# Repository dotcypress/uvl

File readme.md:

# UVL

UV Lamp PCB for 3mm LED's.

## License

Licensed under either of

- Apache License, Version 2.0 ([LICENSE-APACHE](LICENSE-APACHE) or
  http://www.apache.org/licenses/LICENSE-2.0)
- MIT license ([LICENSE-MIT](LICENSE-MIT) or http://opensource.org/licenses/MIT)

at your option.

### Contribution

Unless you explicitly state otherwise, any contribution intentionally submitted
for inclusion in the work by you, as defined in the Apache-2.0 license, shall be
dual licensed as above, without any additional terms or conditions.

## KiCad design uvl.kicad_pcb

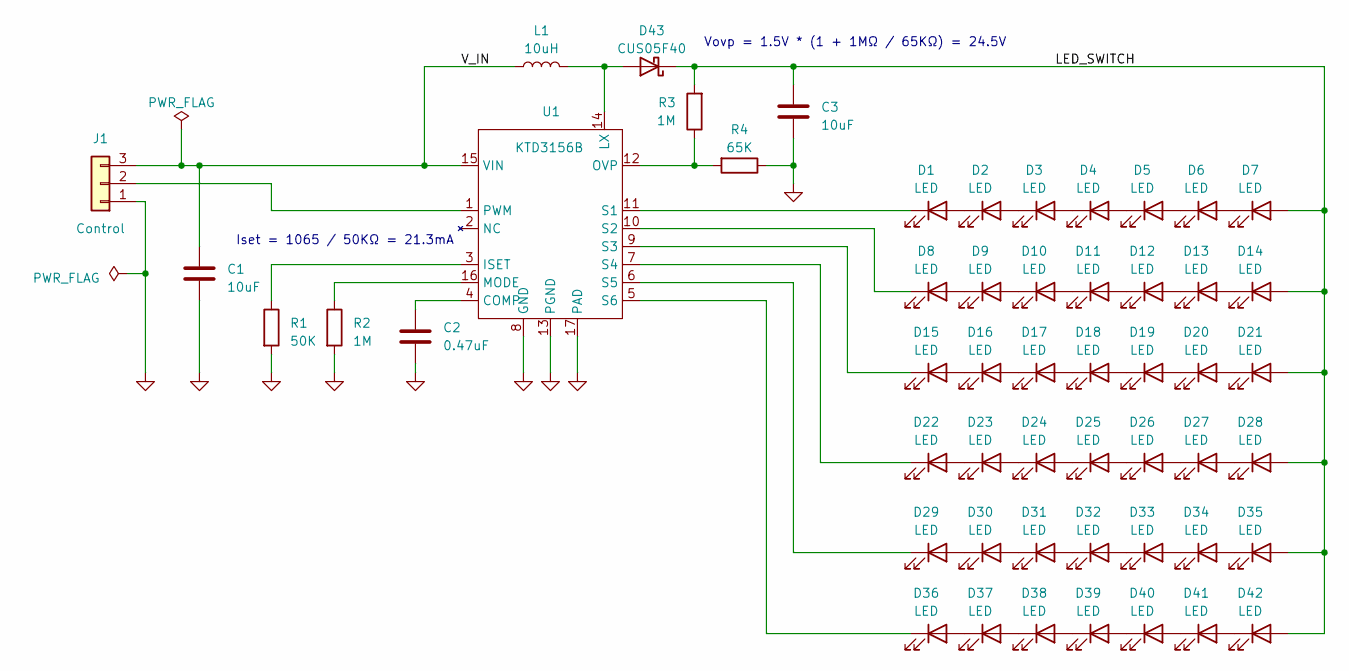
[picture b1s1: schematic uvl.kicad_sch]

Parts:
C1, C3: 10uF; C_0603_1608Metric
C2: 0.47uF; C_0603_1608Metric
D1, D2, D3, D4, D5, D6, D7, D8, D9, D10, D11, D12, D13, D14, D15, D16, D17, D18, D19, D20, D21, D22, D23, D24, D25, D26, D27, D28, D29, D30, D31, D32, D33, D34, D35, D36, D37, D38, D39, D40, D41, D42: LED; LED_D1.8mm_W3.3mm_H2.4mm
D43: CUS05F40; D_SOD-323_HandSoldering
J1: Control; PinHeader_1x03_P2.54mm_Vertical
L1: 10uH; L_Bourns-SRN6028
R1: 50K; R_0603_1608Metric
R2, R3: 1M; R_0603_1608Metric
R4: 65K; R_0603_1608Metric
U1: KTD3156B; QFN-16-1EP_3x3mm_P0.5mm_EP1.7x1.7mm

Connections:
/LED_SWITCH: C3.1, D7.2 (A), D14.2 (A), D21.2 (A), D28.2 (A), D35.2 (A), D42.2 (A), D43.1 (K), R3.2
/V_IN: C1.1, J1.3, L1.1, U1.15 (VIN)
GND: C1.2, C2.2, C3.2, J1.1, R1.2, R2.2, R4.1, U1.8 (GND), U1.13 (PGND), U1.17 (PAD)
unnamed: D1.2 (A), D2.1 (K)
unnamed: D1.1 (K), U1.11 (S1)
unnamed: D2.2 (A), D3.1 (K)
unnamed: D3.2 (A), D4.1 (K)
unnamed: D4.2 (A), D5.1 (K)
unnamed: D5.2 (A), D6.1 (K)
unnamed: D6.2 (A), D7.1 (K)
unnamed: D8.2 (A), D9.1 (K)
unnamed: D8.1 (K), U1.10 (S2)
unnamed: D10.2 (A), D11.1 (K)
unnamed: D9.2 (A), D10.1 (K)
unnamed: D11.2 (A), D12.1 (K)
unnamed: D12.2 (A), D13.1 (K)
unnamed: D13.2 (A), D14.1 (K)
unnamed: D15.2 (A), D16.1 (K)
unnamed: D15.1 (K), U1.9 (S3)
unnamed: D16.2 (A), D17.1 (K)
unnamed: D17.2 (A), D18.1 (K)
unnamed: D18.2 (A), D19.1 (K)
unnamed: D19.2 (A), D20.1 (K)
unnamed: D20.2 (A), D21.1 (K)
unnamed: D22.2 (A), D23.1 (K)
unnamed: D22.1 (K), U1.7 (S4)
unnamed: D23.2 (A), D24.1 (K)
unnamed: D24.2 (A), D25.1 (K)
unnamed: D25.2 (A), D26.1 (K)
unnamed: D26.2 (A), D27.1 (K)
unnamed: D27.2 (A), D28.1 (K)
unnamed: D29.2 (A), D30.1 (K)
unnamed: D29.1 (K), U1.6 (S5)
unnamed: D30.2 (A), D31.1 (K)
unnamed: D31.2 (A), D32.1 (K)
unnamed: D32.2 (A), D33.1 (K)
unnamed: D33.2 (A), D34.1 (K)
unnamed: D34.2 (A), D35.1 (K)
unnamed: D36.2 (A), D37.1 (K)
unnamed: D36.1 (K), U1.5 (S6)
unnamed: D37.2 (A), D38.1 (K)
unnamed: D38.2 (A), D39.1 (K)
unnamed: D39.2 (A), D40.1 (K)
unnamed: D40.2 (A), D41.1 (K)
unnamed: D41.2 (A), D42.1 (K)
unnamed: D43.2 (A), L1.2, U1.14 (LX)
unnamed: J1.2, U1.1 (PWM)
unnamed: C2.1, U1.4 (COMP)
unnamed: R1.1, U1.3 (ISET)
unnamed: R2.1, U1.16 (MODE)
unnamed: R3.1, R4.2, U1.12 (OVP)

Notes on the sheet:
Vovp = 1.5V * (1 + 1MΩ / 65KΩ) = 24.5V
Iset = 1065 / 50KΩ = 21.3mA

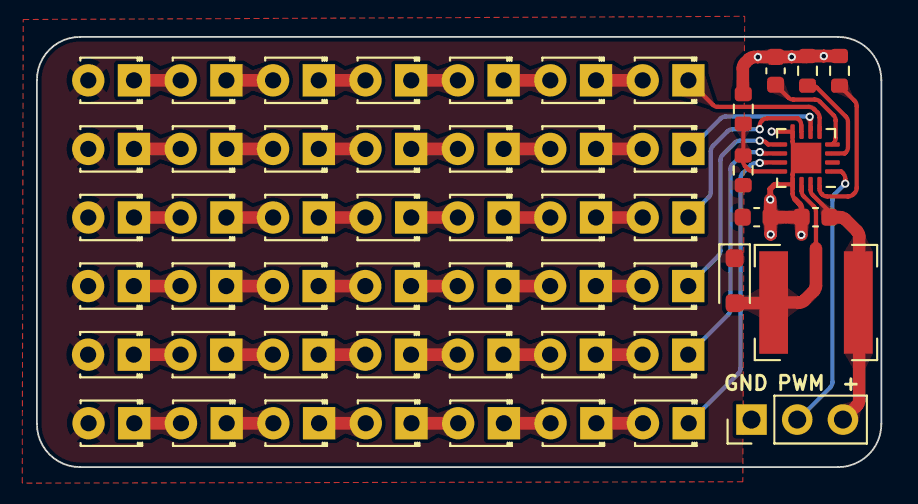
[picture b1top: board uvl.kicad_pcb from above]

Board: 2 copper layers, 46.9 x 23.9 mm, 53 parts (0 on the bottom side), 51 nets.

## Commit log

2023-04-23 rev 0x01
